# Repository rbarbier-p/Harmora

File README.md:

### Things to improve PCB:

- Tiny Leds for status, power, reading/writing
- expose more pins 
- thicker lines if we have the space

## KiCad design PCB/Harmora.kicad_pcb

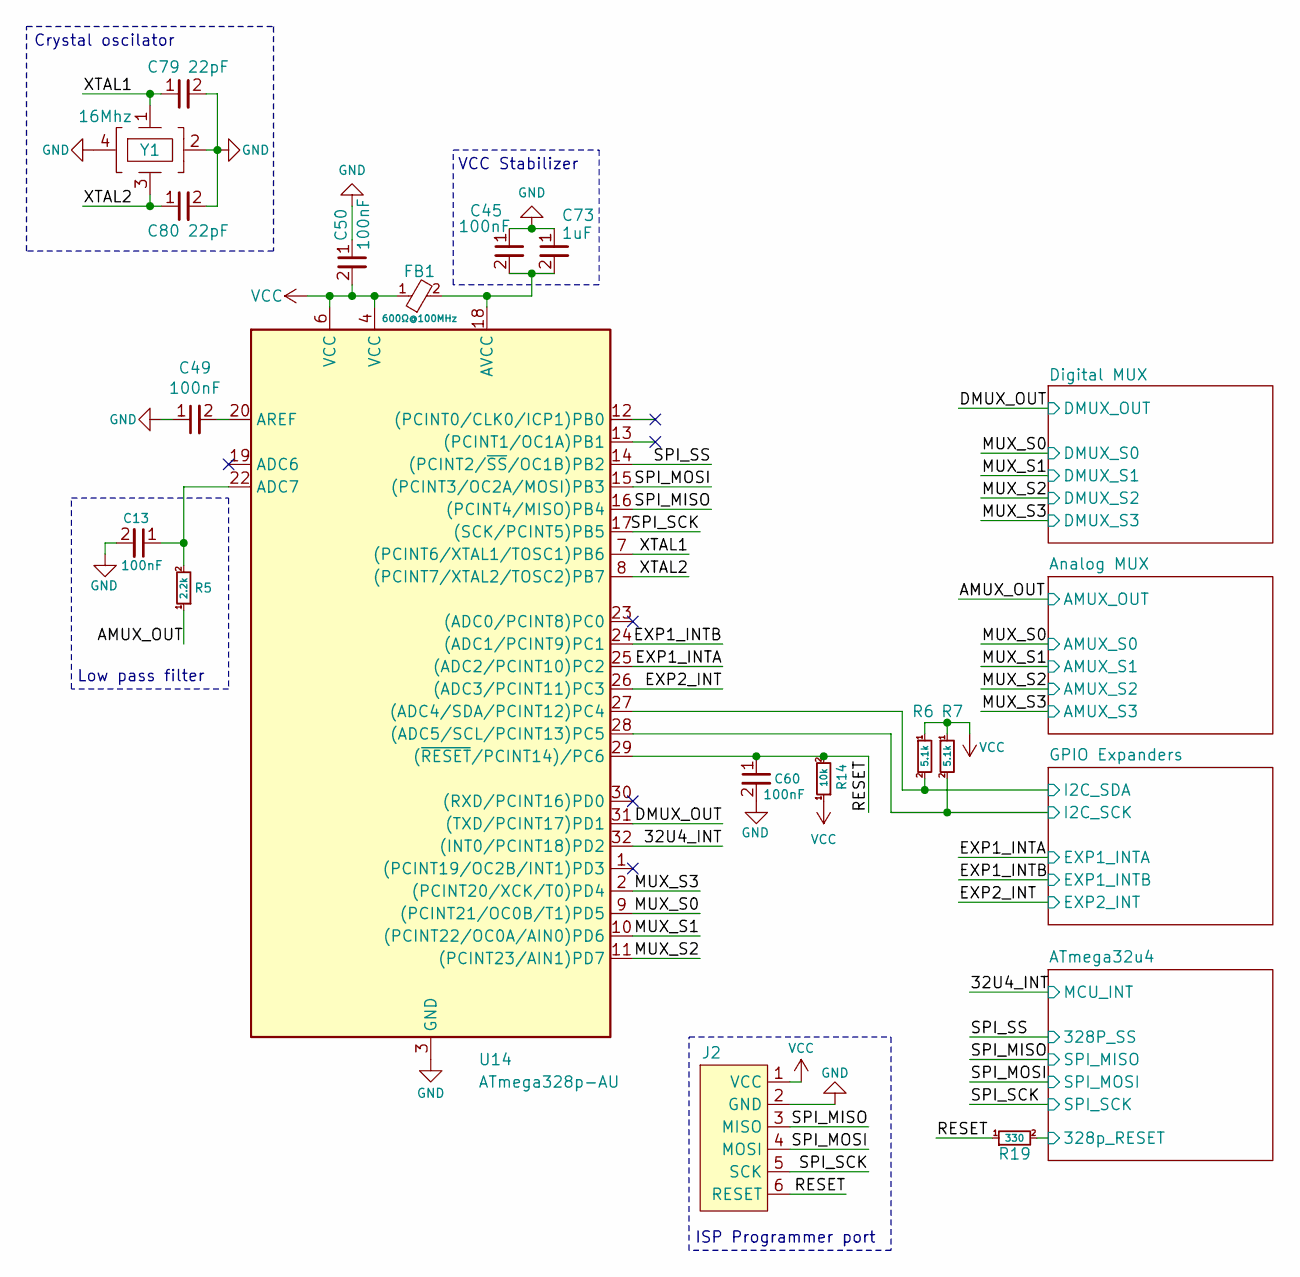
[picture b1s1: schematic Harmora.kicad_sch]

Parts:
C13, C45, C49, C50, C60: 100nF; 0603_C
C73: 1uF; 0603_C
C79, C80: 22pF; 0603_C
FB1: 600Ω@100MHz; 0603_FB
J2: ISP port
R5: 2.2k; 0603_R
R6, R7: 5.1k; 0603_R
R14: 10k; 0603_R
R19: 330; 0603_R
U14: ATmega328p-AU; ATMEGA328P-AU
Y1: 16Mhz; Crystal Oscillator 16MHz

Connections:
/32U4_INT: U14.32 ((INT0/PCINT18)PD2); also elsewhere on the board
/AMUX_OUT: R5.1; also elsewhere on the board
/ATmega32u4/328p_RESET: R19.2; also elsewhere on the board
/DMUX_OUT: U14.31 ((TXD/PCINT17)PD1); also elsewhere on the board
/EXP1_INTA: U14.25 ((ADC2/PCINT10)PC2); also elsewhere on the board
/EXP1_INTB: U14.24 ((ADC1/PCINT9)PC1); also elsewhere on the board
/EXP2_INT: U14.26 ((ADC3/PCINT11)PC3); also elsewhere on the board
/GPIO Expanders/I2C_SCK: R7.2, U14.28 ((ADC5/SCL/PCINT13)PC5); also elsewhere on the board
/GPIO Expanders/I2C_SDA: R6.2, U14.27 ((ADC4/SDA/PCINT12)PC4); also elsewhere on the board
/MUX_S0: U14.9 ((PCINT21/OC0B/T1)PD5); also elsewhere on the board
/MUX_S1: U14.10 ((PCINT22/OC0A/AIN0)PD6); also elsewhere on the board
/MUX_S2: U14.11 ((PCINT23/AIN1)PD7); also elsewhere on the board
/MUX_S3: U14.2 ((PCINT20/XCK/T0)PD4); also elsewhere on the board
/RESET: C60.1, J2.6 (RESET), R14.2, R19.1, U14.29 ((~RESET/PCINT14)/PC6)
/SPI_MISO: J2.3 (MISO), U14.16 ((PCINT4/MISO)PB4); also elsewhere on the board
/SPI_SS: U14.14 ((PCINT2/~SS/OC1B)PB2); also elsewhere on the board
/XTAL1: C79.1, U14.7 ((PCINT6/XTAL1/TOSC1)PB6), Y1.1
/XTAL2: C80.1, U14.8 ((PCINT7/XTAL2/TOSC2)PB7), Y1.3
GND: C13.2, C45.1, C49.1, C50.1, C60.2, C73.1, C79.2, C80.2, J2.2 (GND), U14.3 (GND), Y1.2, Y1.4; also elsewhere on the board
unnamed: C13.1, R5.2, U14.22 (ADC7)
unnamed: C49.2, U14.20 (AREF)
unnamed: C45.2, C73.2, FB1.2, U14.18 (AVCC)
VCC: C50.2, FB1.1, J2.1 (VCC), R6.1, R7.1, R14.1, U14.4 (VCC), U14.6 (VCC); also elsewhere on the board

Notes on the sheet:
ISP Programmer port
Crystal oscilator
Low pass filter
VCC Stabilizer

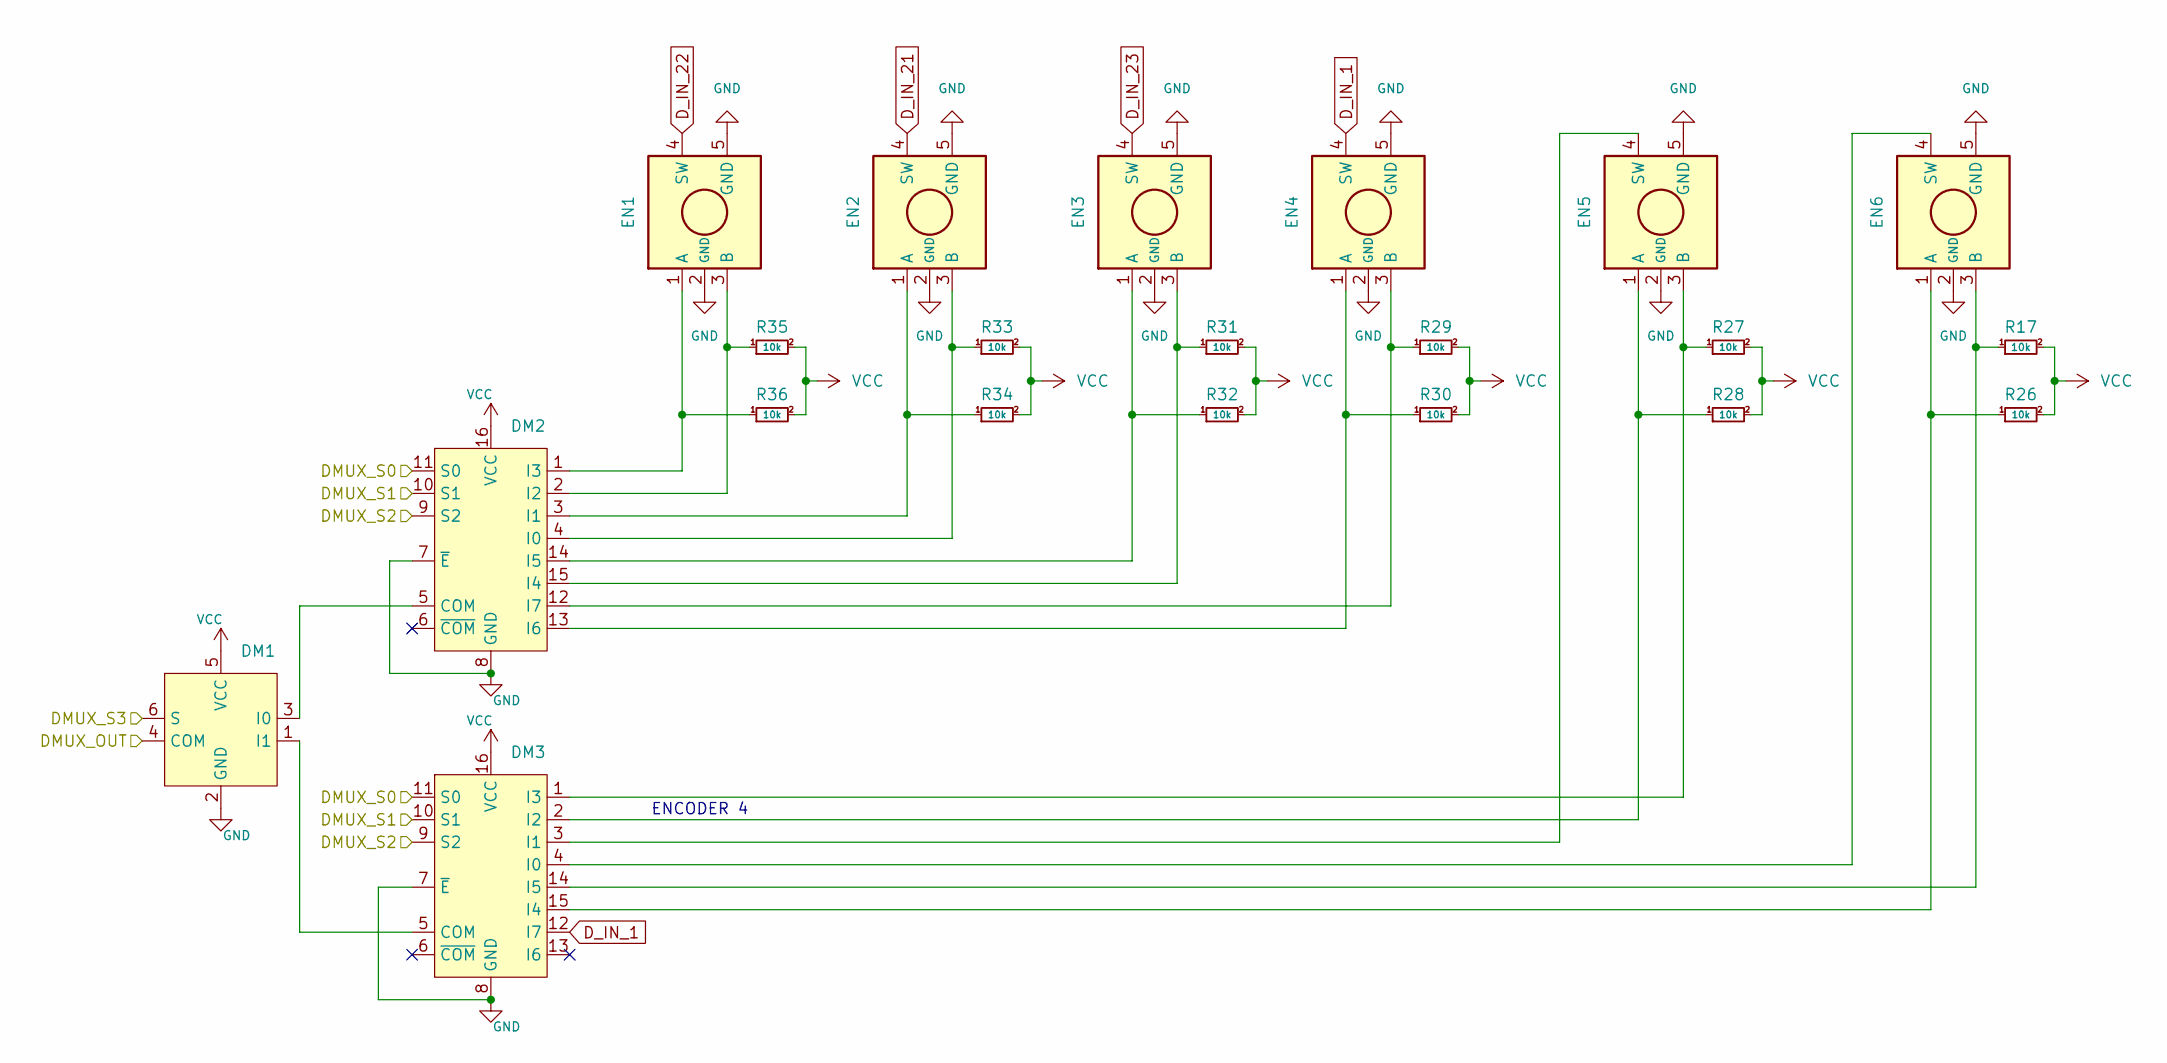
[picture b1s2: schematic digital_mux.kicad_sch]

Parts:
DM1: 74LVC1G157; 74LVC1G157 SOT-363 2_1 MUX
DM2, DM3: 74AC151SC; 74AC151SC SOIC-16 8_1 MUX
EN1, EN2, EN3, EN4, EN5, EN6: Rotary Encoder EC11E
R17, R26, R27, R28, R29, R30, R31, R32, R33, R34, R35, R36: 10k; 0603_R

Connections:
/DMUX_OUT: DM1.4 (COM); also elsewhere on the board
/MUX_S0: DM2.11 (S0), DM3.11 (S0); also elsewhere on the board
/MUX_S1: DM2.10 (S1), DM3.10 (S1); also elsewhere on the board
/MUX_S2: DM2.9 (S2), DM3.9 (S2); also elsewhere on the board
/MUX_S3: DM1.6 (S); also elsewhere on the board
D_IN_1: DM3.12 (I7), EN4.4 (SW)
D_IN_21: EN2.4 (SW); also elsewhere on the board
D_IN_22: EN1.4 (SW); also elsewhere on the board
D_IN_23: EN3.4 (SW); also elsewhere on the board
GND: DM1.2 (GND), DM2.7 (~E), DM2.8 (GND), DM3.7 (~E), DM3.8 (GND), EN1.2 (GND), EN1.5 (GND), EN2.2 (GND), EN2.5 (GND), EN3.2 (GND), EN3.5 (GND), EN4.2 (GND), EN4.5 (GND), EN5.2 (GND), EN5.5 (GND), EN6.2 (GND), EN6.5 (GND); also elsewhere on the board
unnamed: DM1.3 (I0), DM2.5 (COM)
unnamed: DM1.1 (I1), DM3.5 (COM)
unnamed: DM2.4 (I0), EN2.3 (B), R33.1
unnamed: DM2.3 (I1), EN2.1 (A), R34.1
unnamed: DM2.2 (I2), EN1.3 (B), R35.1
unnamed: DM2.1 (I3), EN1.1 (A), R36.1
unnamed: DM2.15 (I4), EN3.3 (B), R31.1
unnamed: DM2.14 (I5), EN3.1 (A), R32.1
unnamed: DM2.13 (I6), EN4.1 (A), R30.1
unnamed: DM2.12 (I7), EN4.3 (B), R29.1
unnamed: DM3.4 (I0), EN6.4 (SW)
unnamed: DM3.3 (I1), EN5.4 (SW)
unnamed: DM3.2 (I2), EN5.1 (A), R28.1
unnamed: DM3.1 (I3), EN5.3 (B), R27.1
unnamed: DM3.15 (I4), EN6.1 (A), R26.1
unnamed: DM3.14 (I5), EN6.3 (B), R17.1
VCC: DM1.5 (VCC), DM2.16 (VCC), DM3.16 (VCC), R17.2, R26.2, R27.2, R28.2, R29.2, R30.2, R31.2, R32.2, R33.2, R34.2, R35.2, R36.2; also elsewhere on the board

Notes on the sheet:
ENCODER 4

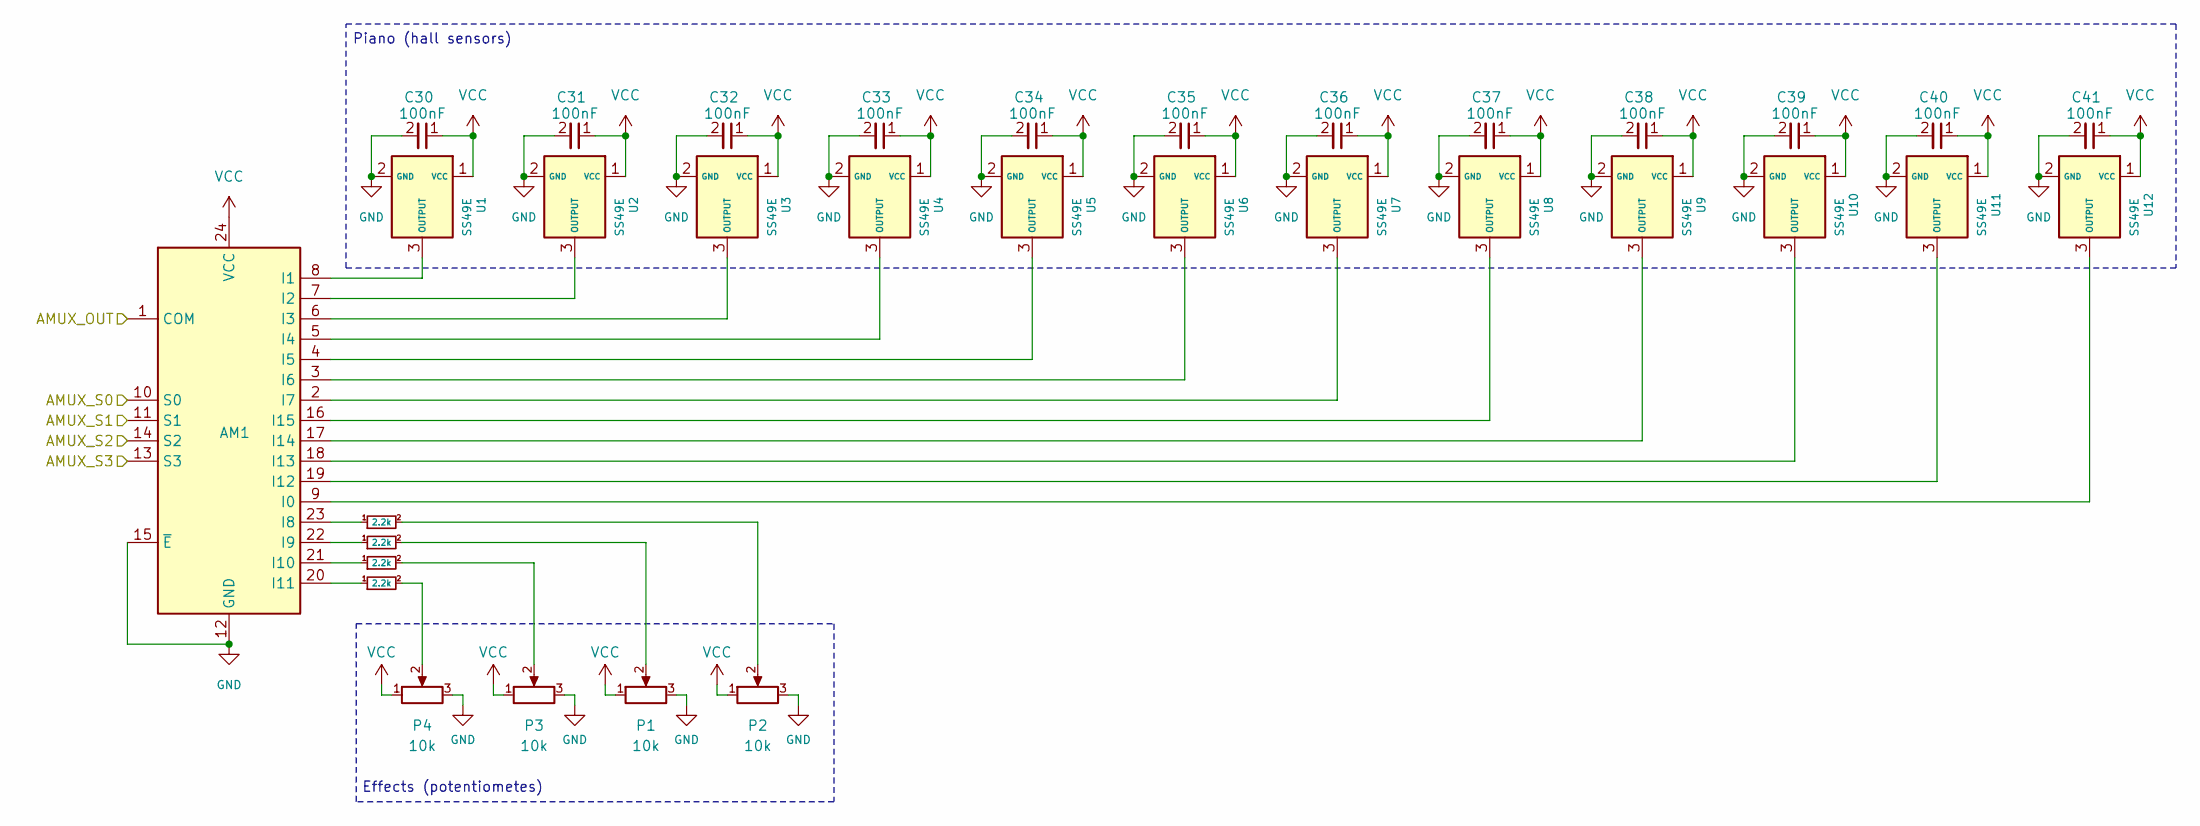
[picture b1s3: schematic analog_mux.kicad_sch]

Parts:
AM1: CD74HC4067M; CD74HC4067M Analog Mux (SOIC-24)
C30, C31, C32, C33, C34, C35, C36, C37, C38, C39, C40, C41: 100nF; 0603_C
P1, P2, P3, P4: 10k; Rotary Potentiometer RK09
R1, R2, R3, R4: 2.2k; 0603_R
U1, U2, U3, U4, U5, U6, U7, U8, U9, U10, U11, U12: SS49E; SLSS49E-3 Hall Sensor (SOT-23-3)

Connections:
/AMUX_OUT: AM1.1 (COM); also elsewhere on the board
/MUX_S0: AM1.10 (S0); also elsewhere on the board
/MUX_S1: AM1.11 (S1); also elsewhere on the board
/MUX_S2: AM1.14 (S2); also elsewhere on the board
/MUX_S3: AM1.13 (S3); also elsewhere on the board
GND: AM1.12 (GND), AM1.15 (~E), C30.2, C31.2, C32.2, C33.2, C34.2, C35.2, C36.2, C37.2, C38.2, C39.2, C40.2, C41.2, P1.3, P2.3, P3.3, P4.3, U1.2 (GND), U2.2 (GND), U3.2 (GND), U4.2 (GND), U5.2 (GND), U6.2 (GND), U7.2 (GND), U8.2 (GND), U9.2 (GND), U10.2 (GND), U11.2 (GND), U12.2 (GND); also elsewhere on the board
unnamed: AM1.9 (I0), U12.3 (OUTPUT)
unnamed: AM1.8 (I1), U1.3 (OUTPUT)
unnamed: AM1.7 (I2), U2.3 (OUTPUT)
unnamed: AM1.6 (I3), U3.3 (OUTPUT)
unnamed: AM1.5 (I4), U4.3 (OUTPUT)
unnamed: AM1.4 (I5), U5.3 (OUTPUT)
unnamed: AM1.3 (I6), U6.3 (OUTPUT)
unnamed: AM1.2 (I7), U7.3 (OUTPUT)
unnamed: AM1.23 (I8), R4.1
unnamed: AM1.22 (I9), R3.1
unnamed: AM1.21 (I10), R2.1
unnamed: AM1.20 (I11), R1.1
unnamed: AM1.19 (I12), U11.3 (OUTPUT)
unnamed: AM1.18 (I13), U10.3 (OUTPUT)
unnamed: AM1.17 (I14), U9.3 (OUTPUT)
unnamed: AM1.16 (I15), U8.3 (OUTPUT)
unnamed: P1.2, R3.2
unnamed: P2.2, R4.2
unnamed: P3.2, R2.2
unnamed: P4.2, R1.2
VCC: AM1.24 (VCC), C30.1, C31.1, C32.1, C33.1, C34.1, C35.1, C36.1, C37.1, C38.1, C39.1, C40.1, C41.1, P1.1, P2.1, P3.1, P4.1, U1.1 (VCC), U2.1 (VCC), U3.1 (VCC), U4.1 (VCC), U5.1 (VCC), U6.1 (VCC), U7.1 (VCC), U8.1 (VCC), U9.1 (VCC), U10.1 (VCC), U11.1 (VCC), U12.1 (VCC); also elsewhere on the board

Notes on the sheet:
Piano (hall sensors)
Effects (potentiometes)

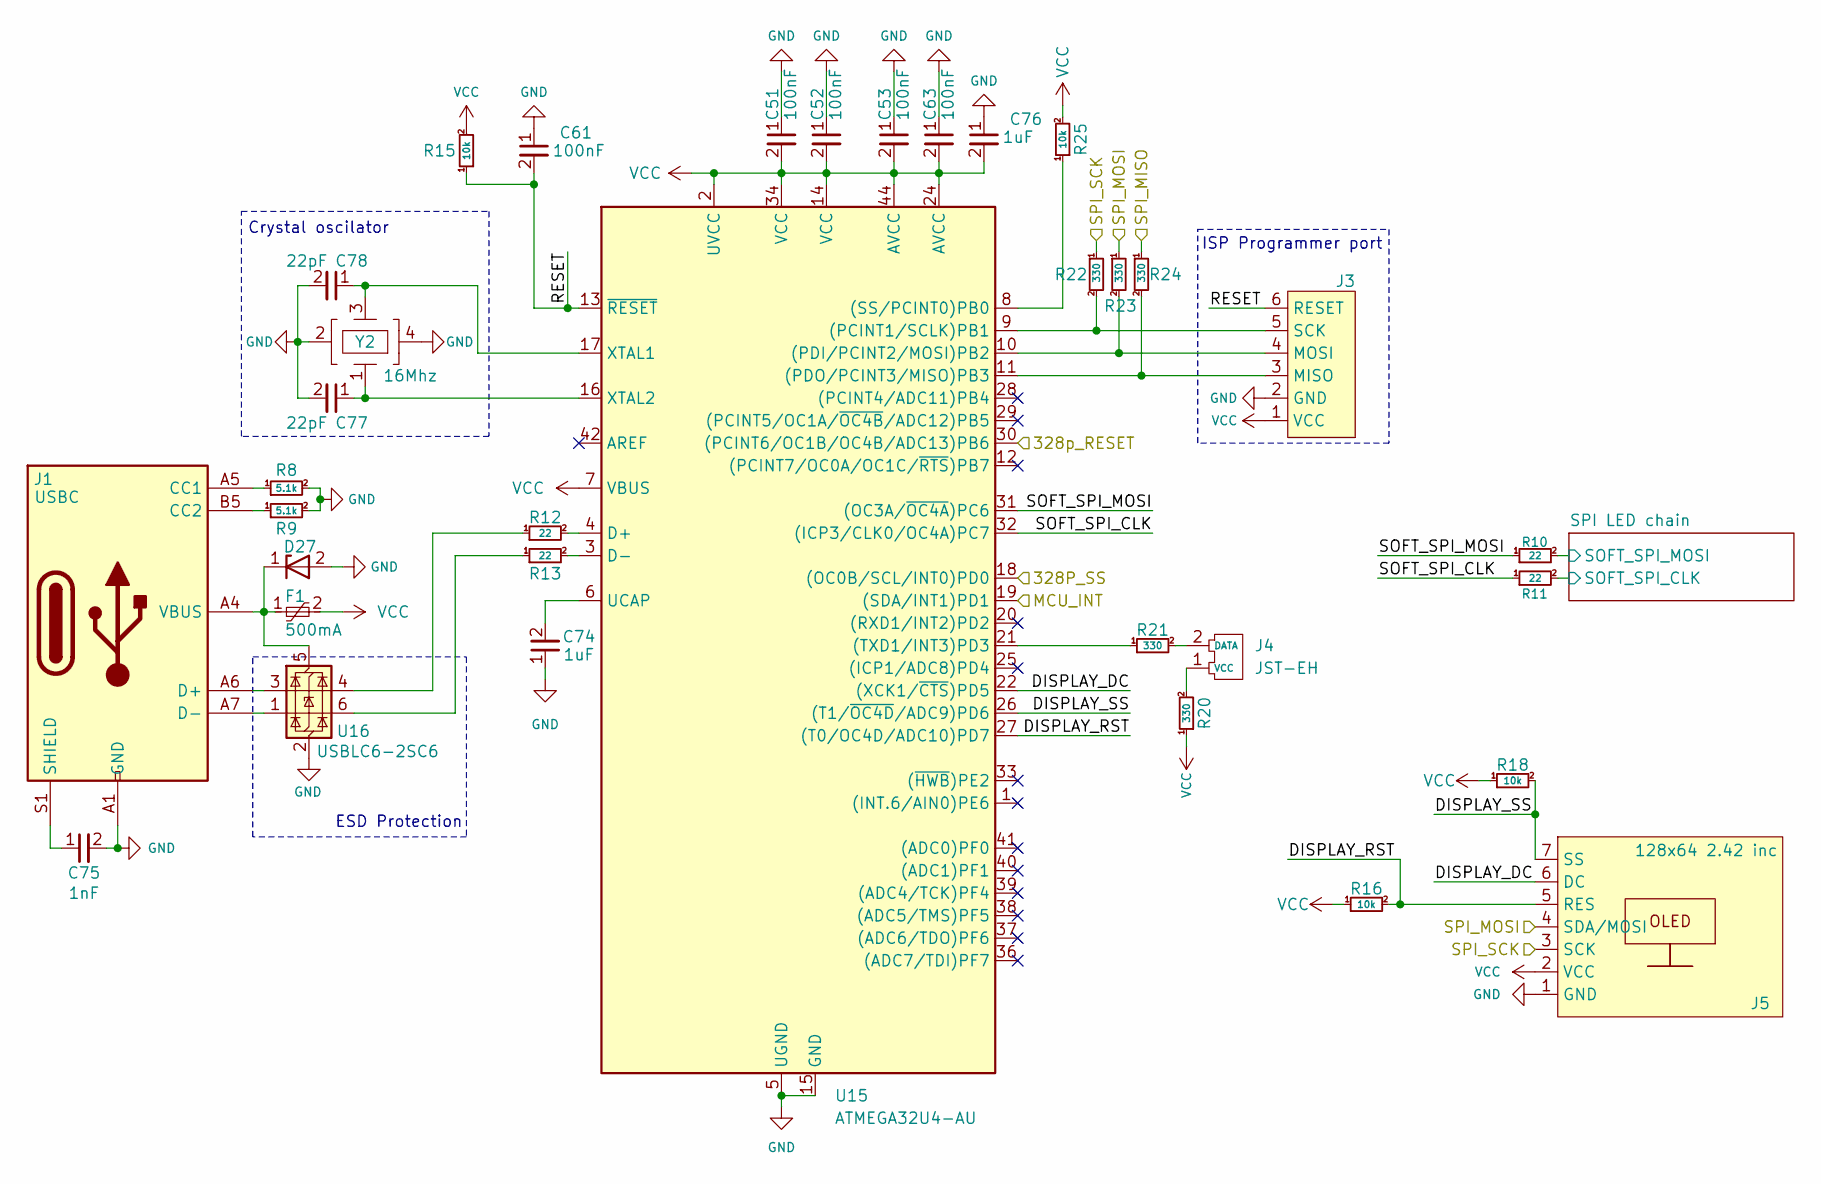
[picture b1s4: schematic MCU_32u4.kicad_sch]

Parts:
C51, C52, C53, C61, C63: 100nF; 0603_C
C74, C76: 1uF; 0603_C
C75: 1nF; 0603_C
C77, C78: 22pF; 0603_C
D27: TVS Diode SOD-123FL
F1: 500mA; Resettable Fuse 1206
J1: USBC; USB C Receptacle USB2.0 16PIN
J3: ISP port
J4: JST-EH; JST-EH port
J5: 128x64 2.42 inc; SPI Screen PinHeader
R8, R9: 5.1k; 0603_R
R10, R11, R12, R13: 22; 0603_R
R15, R16, R18, R25: 10k; 0603_R
R20, R21, R22, R23, R24: 330; 0603_R
U15: ATMEGA32U4-AU
U16: USBLC6-2SC6; ESD Prot SOT-23-6
Y2: 16Mhz; Crystal Oscillator 16MHz

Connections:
/32U4_INT: U15.19 ((SDA/INT1)PD1); also elsewhere on the board
/ATmega32u4/328p_RESET: U15.30 ((PCINT6/OC1B/OC4B/ADC13)PB6); also elsewhere on the board
/ATmega32u4/DISPLAY_DC: J5.6 (DC), U15.22 ((XCK1/~CTS)PD5)
/ATmega32u4/DISPLAY_RST: J5.5 (RES), R16.2, U15.27 ((T0/OC4D/ADC10)PD7)
/ATmega32u4/DISPLAY_SS: J5.7 (SS), R18.2, U15.26 ((T1/~OC4D/ADC9)PD6)
/ATmega32u4/RESET: C61.2, J3.6 (RESET), R15.1, U15.13 (~RESET)
/ATmega32u4/SOFT_SPI_CLK: R11.1, U15.32 ((ICP3/CLK0/OC4A)PC7)
/ATmega32u4/SOFT_SPI_MOSI: R10.1, U15.31 ((OC3A/~OC4A)PC6)
/ATmega32u4/SPI LED chain/SOFT_SPI_CLK: R11.2; also elsewhere on the board
/ATmega32u4/SPI LED chain/SOFT_SPI_MOSI: R10.2; also elsewhere on the board
/SPI_MISO: R24.1; also elsewhere on the board
/SPI_SS: U15.18 ((OC0B/SCL/INT0)PD0); also elsewhere on the board
GND: C51.1, C52.1, C53.1, C61.1, C63.1, C74.1, C75.2, C76.1, C77.2, C78.2, D27.2, J1.A1 (GND), J1.A12 (GND), J1.B1 (GND), J1.B12 (GND), J3.2 (GND), J5.1 (GND), R8.2, R9.2, U15.5 (UGND), U15.15 (GND), U16.2 (GND), Y2.2, Y2.4; also elsewhere on the board
unnamed: J1.A5 (CC1), R8.1
unnamed: J1.B5 (CC2), R9.1
unnamed: J1.A6 (D+), U16.3 (I/O1)
unnamed: J1.A7 (D-), U16.1 (I/O2)
unnamed: C75.1, J1.S1 (SHIELD)
unnamed: D27.1, F1.1, J1.A4 (VBUS), U16.5 (VBUS)
unnamed: J3.3 (MISO), R24.2, U15.11 ((PDO/PCINT3/MISO)PB3)
unnamed: J4.2 (DATA), R21.2
unnamed: J4.1 (VCC), R20.2
unnamed: R12.1, U16.4 (I/O1)
unnamed: R13.1, U16.6 (I/O2)
unnamed: R25.1, U15.8 ((SS/PCINT0)PB0)
unnamed: R21.1, U15.21 ((TXD1/INT3)PD3)
unnamed: R12.2, U15.4 (D+)
unnamed: R13.2, U15.3 (D-)
unnamed: C74.2, U15.6 (UCAP)
unnamed: C78.1, U15.17 (XTAL1), Y2.3
unnamed: C77.1, U15.16 (XTAL2), Y2.1
VCC: C51.2, C52.2, C53.2, C63.2, C76.2, F1.2, J3.1 (VCC), J5.2 (VCC), R15.2, R16.1, R18.1, R20.1, R25.2, U15.2 (UVCC), U15.7 (VBUS), U15.14 (VCC), U15.24 (AVCC), U15.34 (VCC), U15.44 (AVCC); also elsewhere on the board

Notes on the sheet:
ISP Programmer port
ESD Protection
Crystal oscilator

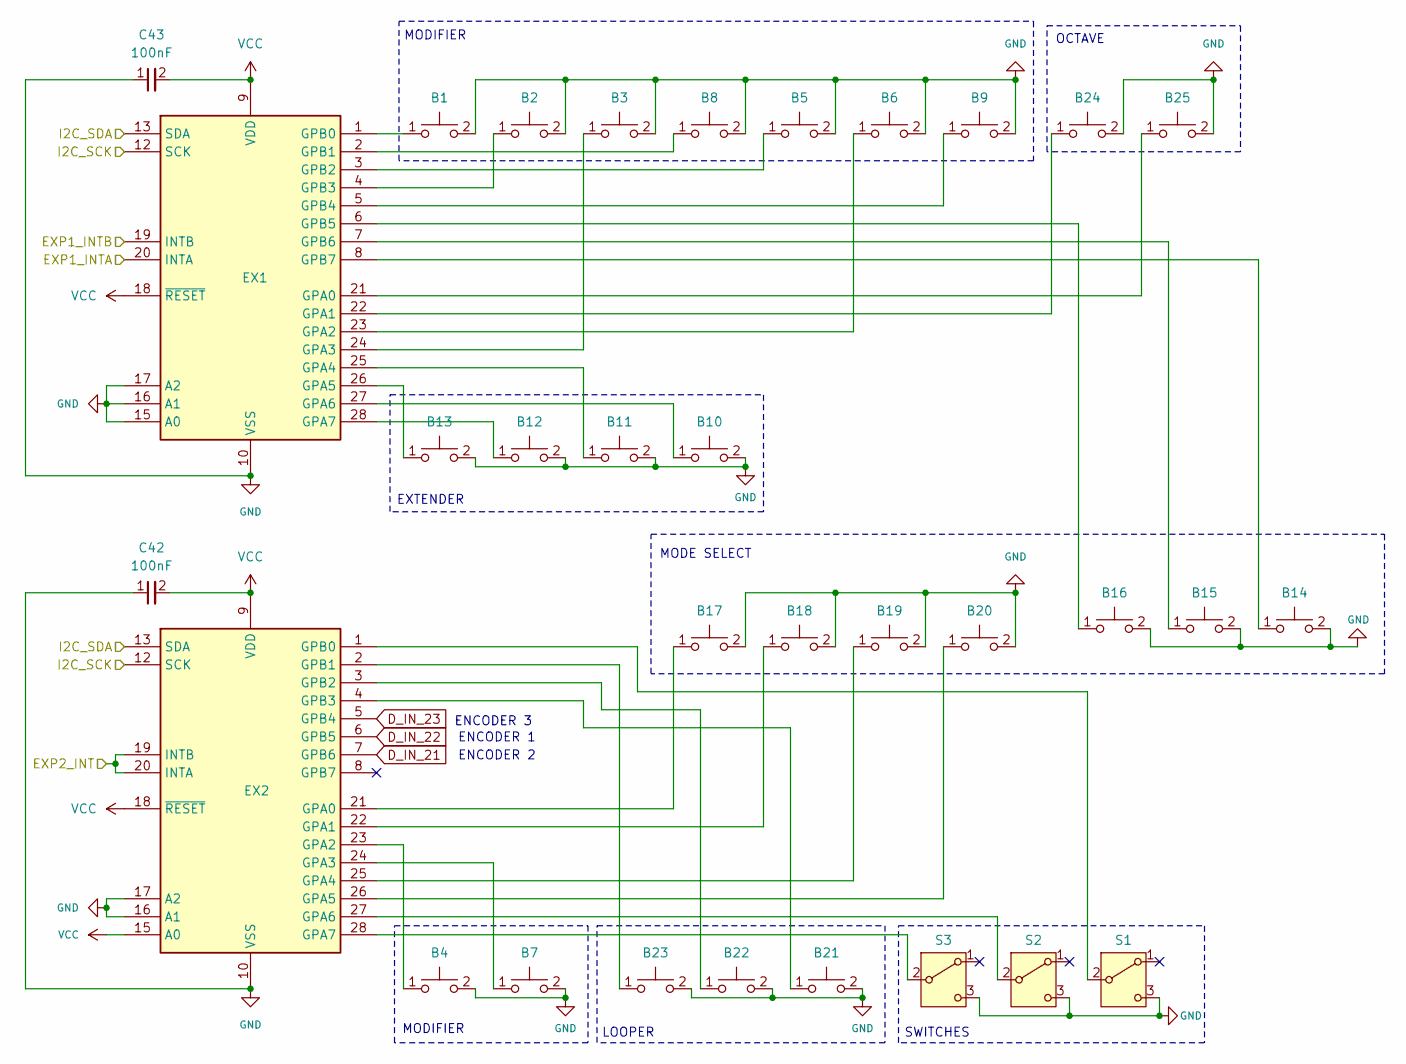
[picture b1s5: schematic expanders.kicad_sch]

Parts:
B1, B2, B3, B4, B5, B6, B7, B8, B9, B10, B11, B12, B13, B14, B15, B16, B17, B18, B19, B20, B21, B22, B23, B24, B25: Mechanical Switch
C42, C43: 100nF; 0603_C
EX1, EX2: MCP23017 GPIO Expander
S1, S2, S3: MTS-102 Switch

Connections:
/EXP1_INTA: EX1.20 (INTA); also elsewhere on the board
/EXP1_INTB: EX1.19 (INTB); also elsewhere on the board
/EXP2_INT: EX2.19 (INTB), EX2.20 (INTA); also elsewhere on the board
/GPIO Expanders/I2C_SCK: EX1.12 (SCK), EX2.12 (SCK); also elsewhere on the board
/GPIO Expanders/I2C_SDA: EX1.13 (SDA), EX2.13 (SDA); also elsewhere on the board
D_IN_21: EX2.7 (GPB6); also elsewhere on the board
D_IN_22: EX2.6 (GPB5); also elsewhere on the board
D_IN_23: EX2.5 (GPB4); also elsewhere on the board
GND: B1.2, B2.2, B3.2, B4.2, B5.2, B6.2, B7.2, B8.2, B9.2, B10.2, B11.2, B12.2, B13.2, B14.2, B15.2, B16.2, B17.2, B18.2, B19.2, B20.2, B21.2, B22.2, B23.2, B24.2, B25.2, C42.1, C43.1, EX1.10 (VSS), EX1.15 (A0), EX1.16 (A1), EX1.17 (A2), EX2.10 (VSS), EX2.16 (A1), EX2.17 (A2), S1.3, S2.3, S3.3; also elsewhere on the board
unnamed: B25.1, EX1.21 (GPA0)
unnamed: B24.1, EX1.22 (GPA1)
unnamed: B6.1, EX1.23 (GPA2)
unnamed: B3.1, EX1.24 (GPA3)
unnamed: B11.1, EX1.25 (GPA4)
unnamed: B13.1, EX1.26 (GPA5)
unnamed: B10.1, EX1.27 (GPA6)
unnamed: B12.1, EX1.28 (GPA7)
unnamed: B1.1, EX1.1 (GPB0)
unnamed: B8.1, EX1.2 (GPB1)
unnamed: B5.1, EX1.3 (GPB2)
unnamed: B2.1, EX1.4 (GPB3)
unnamed: B9.1, EX1.5 (GPB4)
unnamed: B16.1, EX1.6 (GPB5)
unnamed: B15.1, EX1.7 (GPB6)
unnamed: B14.1, EX1.8 (GPB7)
unnamed: B17.1, EX2.21 (GPA0)
unnamed: B18.1, EX2.22 (GPA1)
unnamed: B4.1, EX2.23 (GPA2)
unnamed: B7.1, EX2.24 (GPA3)
unnamed: B19.1, EX2.25 (GPA4)
unnamed: B20.1, EX2.26 (GPA5)
unnamed: EX2.27 (GPA6), S2.2
unnamed: EX2.28 (GPA7), S3.2
unnamed: EX2.1 (GPB0), S1.2
unnamed: B23.1, EX2.2 (GPB1)
unnamed: B22.1, EX2.3 (GPB2)
unnamed: B21.1, EX2.4 (GPB3)
VCC: C42.2, C43.2, EX1.9 (VDD), EX1.18 (~RESET), EX2.9 (VDD), EX2.15 (A0), EX2.18 (~RESET); also elsewhere on the board

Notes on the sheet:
ENCODER 1
LOOPER
MODIFIER
MODE SELECT
EXTENDER
SWITCHES
ENCODER 2
ENCODER 3
OCTAVE

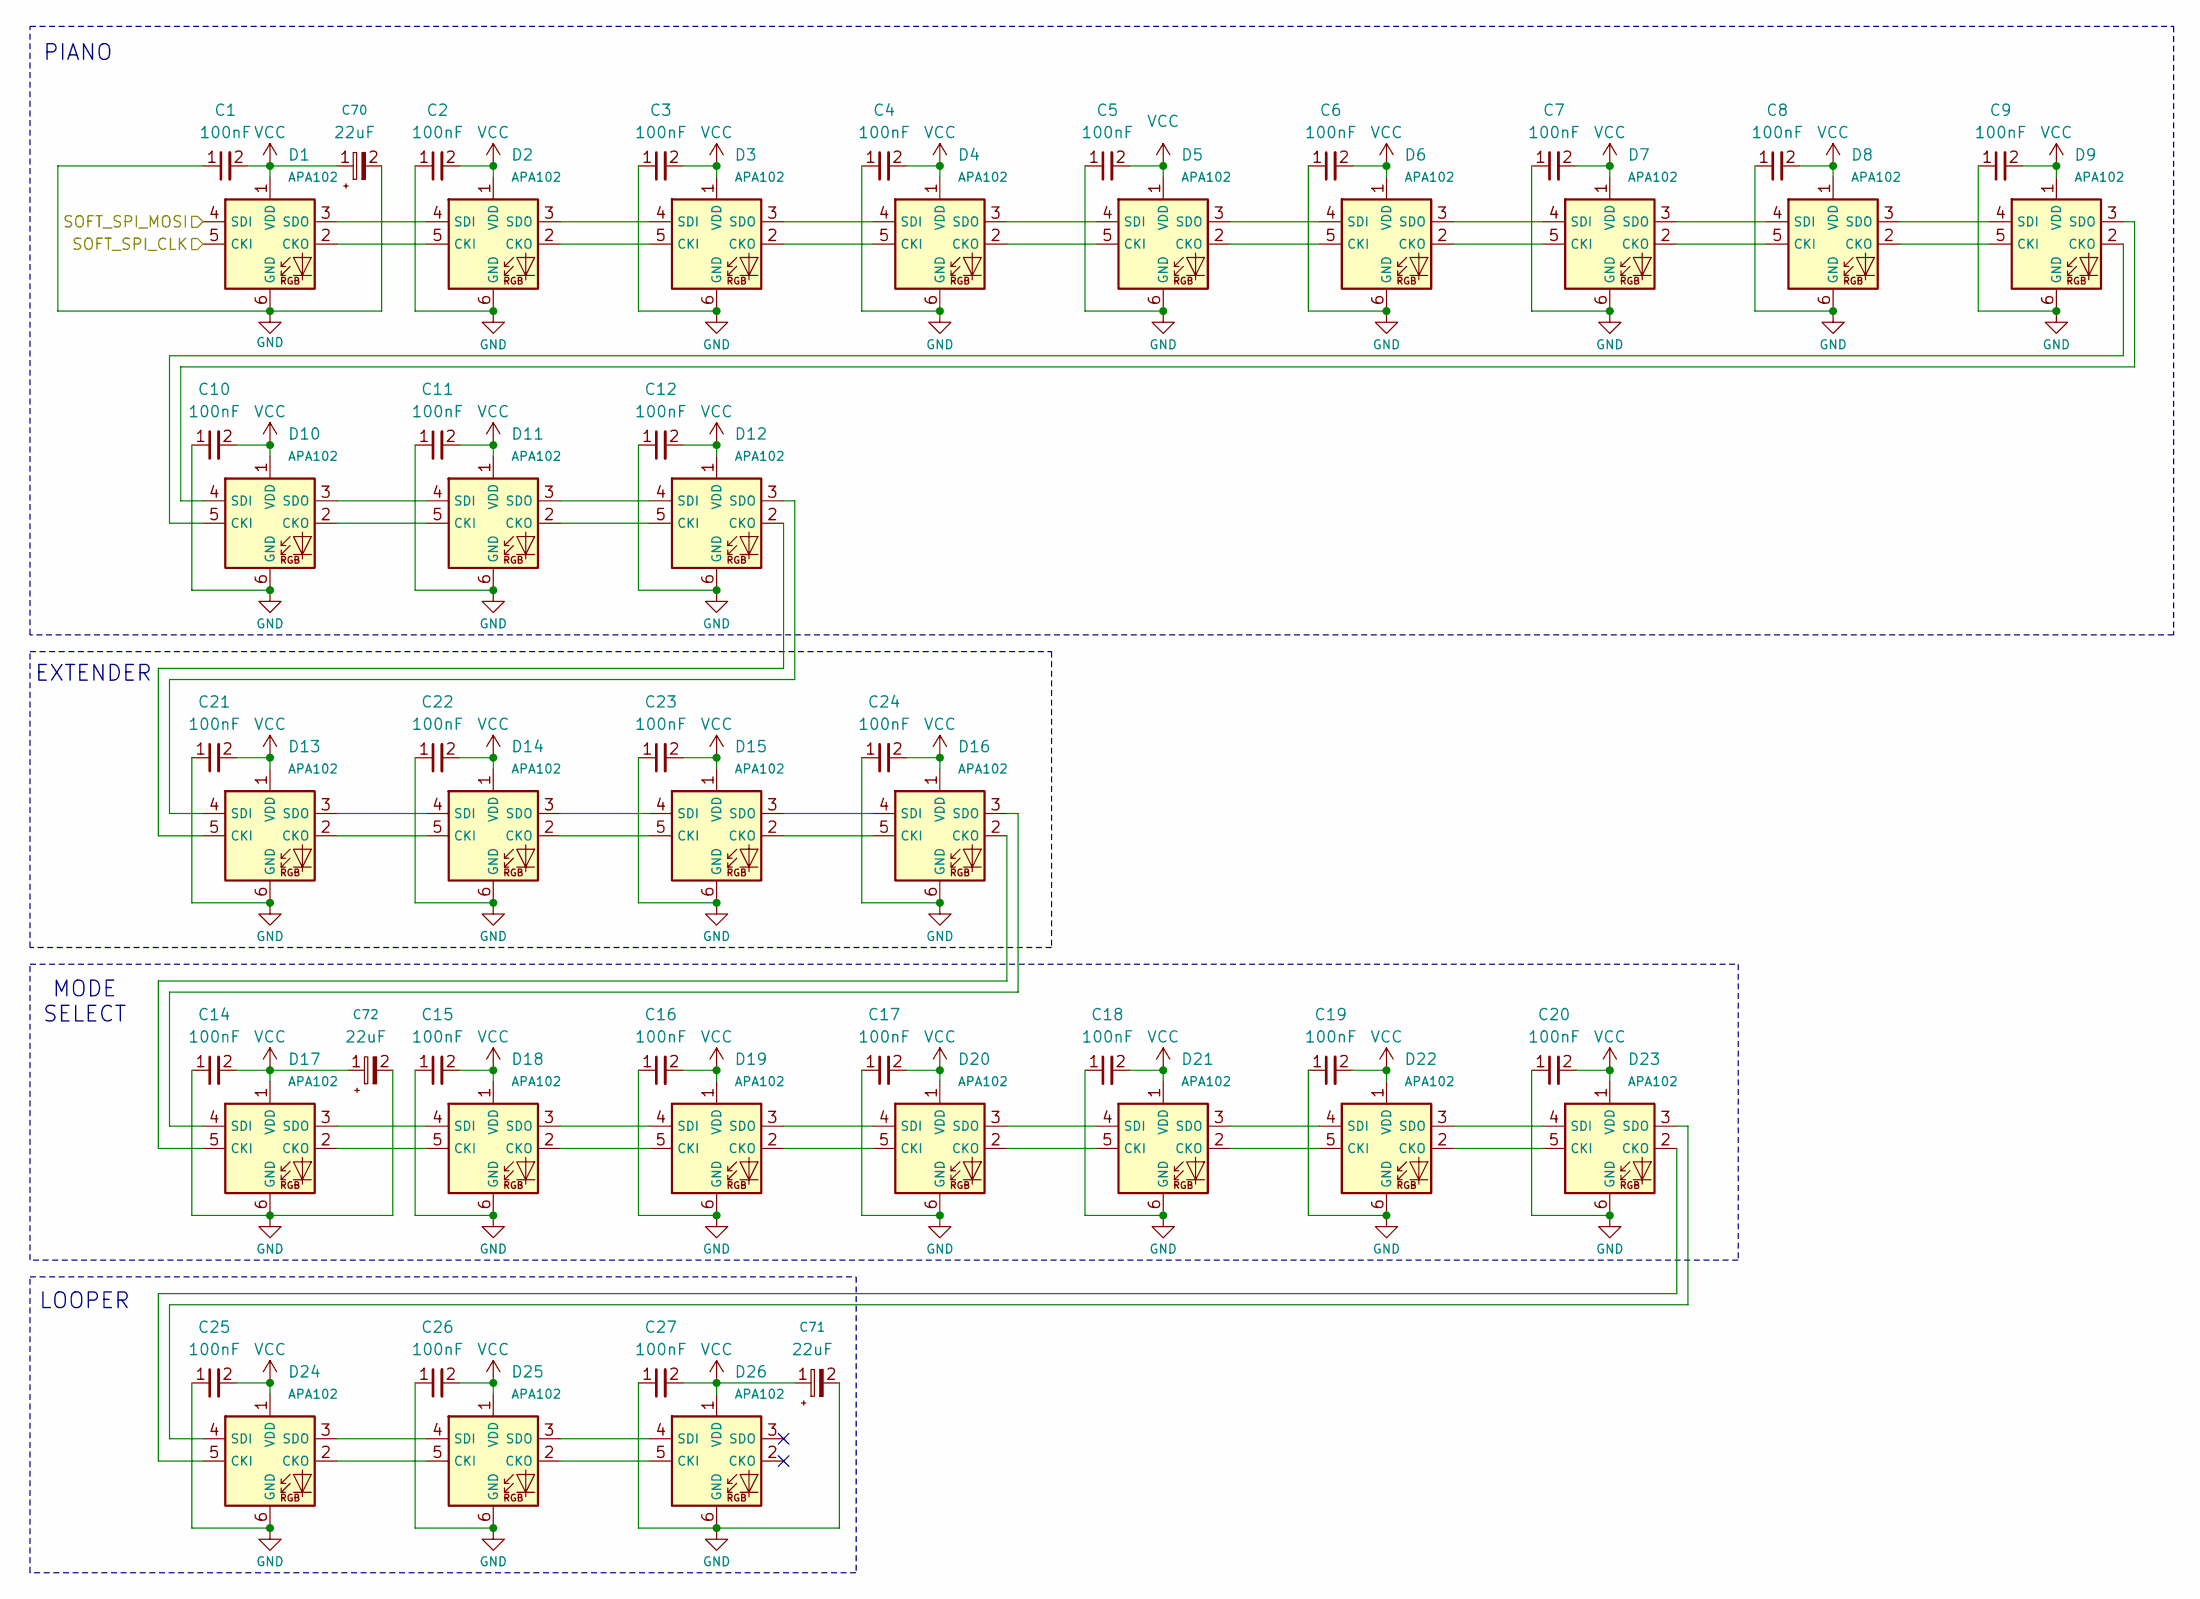
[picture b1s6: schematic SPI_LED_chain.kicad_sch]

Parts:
C1, C2, C3, C4, C5, C6, C7, C8, C9, C10, C11, C12, C14, C15, C16, C17, C18, C19, C20, C21, C22, C23, C24, C25, C26, C27: 100nF; 0603_C
C70, C71, C72: 22uF; C_Electrolytic_4x5.4
D1, D2, D3, D4, D5, D6, D7, D8, D9, D10, D11, D12, D13, D14, D15, D16, D17, D18, D19, D20, D21, D22, D23, D24, D25, D26: APA102; APA102 LED

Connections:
/ATmega32u4/SPI LED chain/SOFT_SPI_CLK: D1.5 (CKI); also elsewhere on the board
/ATmega32u4/SPI LED chain/SOFT_SPI_MOSI: D1.4 (SDI); also elsewhere on the board
GND: C1.1, C2.1, C3.1, C4.1, C5.1, C6.1, C7.1, C8.1, C9.1, C10.1, C11.1, C12.1, C14.1, C15.1, C16.1, C17.1, C18.1, C19.1, C20.1, C21.1, C22.1, C23.1, C24.1, C25.1, C26.1, C27.1, C70.2, C71.2, C72.2, D1.6 (GND), D2.6 (GND), D3.6 (GND), D4.6 (GND), D5.6 (GND), D6.6 (GND), D7.6 (GND), D8.6 (GND), D9.6 (GND), D10.6 (GND), D11.6 (GND), D12.6 (GND), D13.6 (GND), D14.6 (GND), D15.6 (GND), D16.6 (GND), D17.6 (GND), D18.6 (GND), D19.6 (GND), D20.6 (GND), D21.6 (GND), D22.6 (GND), D23.6 (GND), D24.6 (GND), D25.6 (GND), D26.6 (GND); also elsewhere on the board
unnamed: D1.2 (CKO), D2.5 (CKI)
unnamed: D1.3 (SDO), D2.4 (SDI)
unnamed: D2.2 (CKO), D3.5 (CKI)
unnamed: D2.3 (SDO), D3.4 (SDI)
unnamed: D3.2 (CKO), D4.5 (CKI)
unnamed: D3.3 (SDO), D4.4 (SDI)
unnamed: D4.2 (CKO), D5.5 (CKI)
unnamed: D4.3 (SDO), D5.4 (SDI)
unnamed: D5.2 (CKO), D6.5 (CKI)
unnamed: D5.3 (SDO), D6.4 (SDI)
unnamed: D6.2 (CKO), D7.5 (CKI)
unnamed: D6.3 (SDO), D7.4 (SDI)
unnamed: D7.2 (CKO), D8.5 (CKI)
unnamed: D7.3 (SDO), D8.4 (SDI)
unnamed: D8.2 (CKO), D9.5 (CKI)
unnamed: D8.3 (SDO), D9.4 (SDI)
unnamed: D9.2 (CKO), D10.5 (CKI)
unnamed: D10.2 (CKO), D11.5 (CKI)
unnamed: D9.3 (SDO), D10.4 (SDI)
unnamed: D10.3 (SDO), D11.4 (SDI)
unnamed: D11.2 (CKO), D12.5 (CKI)
unnamed: D11.3 (SDO), D12.4 (SDI)
unnamed: D12.2 (CKO), D13.5 (CKI)
unnamed: D12.3 (SDO), D13.4 (SDI)
unnamed: D13.2 (CKO), D14.5 (CKI)
unnamed: D13.3 (SDO), D14.4 (SDI)
unnamed: D14.2 (CKO), D15.5 (CKI)
unnamed: D14.3 (SDO), D15.4 (SDI)
unnamed: D15.2 (CKO), D16.5 (CKI)
unnamed: D15.3 (SDO), D16.4 (SDI)
unnamed: D16.2 (CKO), D17.5 (CKI)
unnamed: D16.3 (SDO), D17.4 (SDI)
unnamed: D17.2 (CKO), D18.5 (CKI)
unnamed: D17.3 (SDO), D18.4 (SDI)
unnamed: D18.2 (CKO), D19.5 (CKI)
unnamed: D18.3 (SDO), D19.4 (SDI)
unnamed: D19.2 (CKO), D20.5 (CKI)
unnamed: D19.3 (SDO), D20.4 (SDI)
unnamed: D20.2 (CKO), D21.5 (CKI)
unnamed: D20.3 (SDO), D21.4 (SDI)
unnamed: D21.2 (CKO), D22.5 (CKI)
unnamed: D21.3 (SDO), D22.4 (SDI)
unnamed: D22.2 (CKO), D23.5 (CKI)
unnamed: D22.3 (SDO), D23.4 (SDI)
unnamed: D23.2 (CKO), D24.5 (CKI)
unnamed: D23.3 (SDO), D24.4 (SDI)
unnamed: D24.2 (CKO), D25.5 (CKI)
unnamed: D24.3 (SDO), D25.4 (SDI)
unnamed: D25.2 (CKO), D26.5 (CKI)
unnamed: D25.3 (SDO), D26.4 (SDI)
VCC: C1.2, C2.2, C3.2, C4.2, C5.2, C6.2, C7.2, C8.2, C9.2, C10.2, C11.2, C12.2, C14.2, C15.2, C16.2, C17.2, C18.2, C19.2, C20.2, C21.2, C22.2, C23.2, C24.2, C25.2, C26.2, C27.2, C70.1, C71.1, C72.1, D1.1 (VDD), D2.1 (VDD), D3.1 (VDD), D4.1 (VDD), D5.1 (VDD), D6.1 (VDD), D7.1 (VDD), D8.1 (VDD), D9.1 (VDD), D10.1 (VDD), D11.1 (VDD), D12.1 (VDD), D13.1 (VDD), D14.1 (VDD), D15.1 (VDD), D16.1 (VDD), D17.1 (VDD), D18.1 (VDD), D19.1 (VDD), D20.1 (VDD), D21.1 (VDD), D22.1 (VDD), D23.1 (VDD), D24.1 (VDD), D25.1 (VDD), D26.1 (VDD); also elsewhere on the board

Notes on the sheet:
MODE SELECT
PIANO
LOOPER
EXTENDER

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
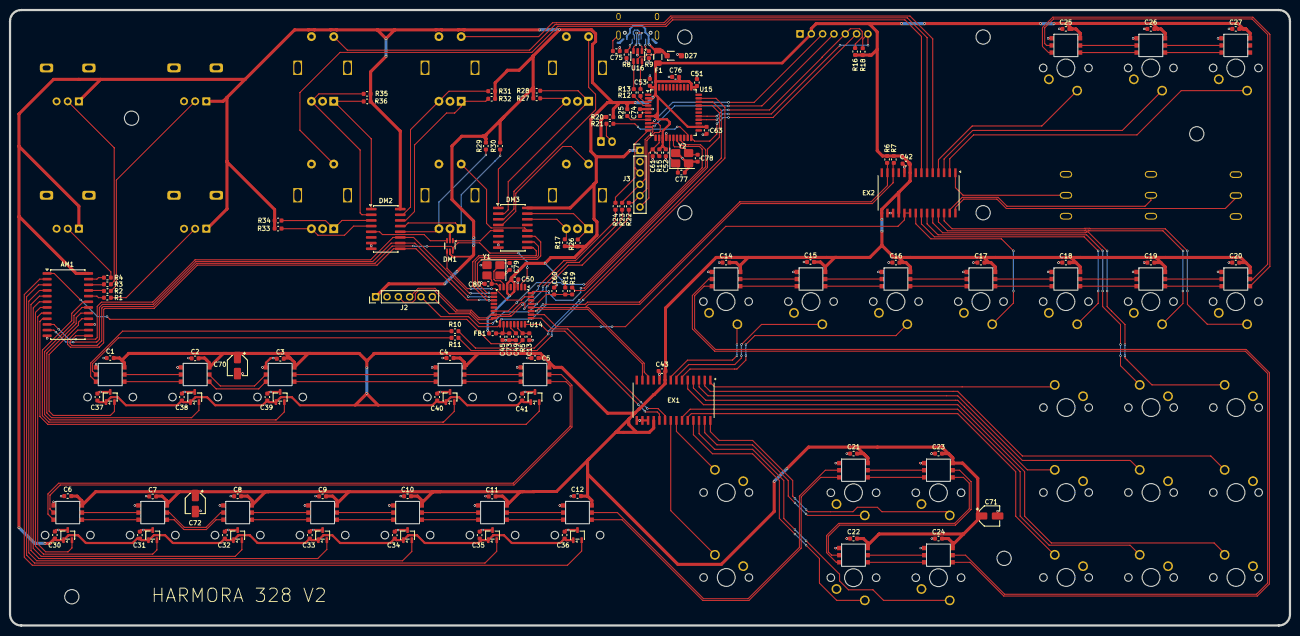
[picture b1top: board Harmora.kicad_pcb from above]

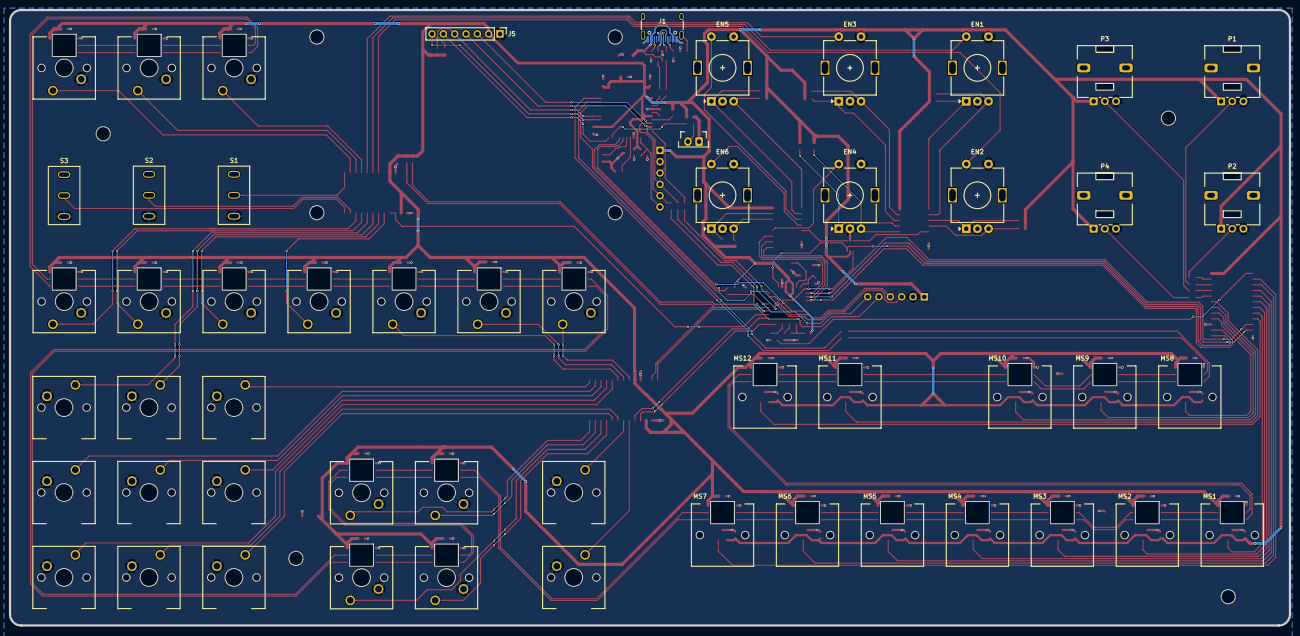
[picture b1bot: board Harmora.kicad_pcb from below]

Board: 2 copper layers, 287.0 x 138.0 mm, 192 parts (41 on the bottom side), 169 nets.
